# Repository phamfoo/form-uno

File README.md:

# Form Uno
> Gasket mounted 5x12 column staggered keyboard

## Introduction
I designed this board with a few goals in mind:

### Ergonomic
The layout is based on the corne/cornelius by [foostan](https://github.com/foostan), with some adjustments:
- Unsplit.
- Number row.
- Options for dedicated arrow keys.

### Fully featured
It also comes with the neat features that you'd find in custom mechanical keyboards:

- Gasket-mounted.
- Hotswap PCB + daughterboard.
- Clean and minimal design.

### Easy to build
- Powered by an [RP2040 Tiny](https://www.waveshare.com/rp2040-tiny.htm) and [all the other parts](build) can be easily sourced.
- No tiny SMD components required!

## Build guide
See [build](/build)

## Thanks
- [JLCPCB](https://jlcpcb.com/?from=see) for providing the keyboard plate, 3D printed case, and PCB for this project. If you're looking to build your own board, I highly recommend their services.
- [foostan](https://github.com/foostan) for creating the corne/cornelius, which inspired this project in the first place.

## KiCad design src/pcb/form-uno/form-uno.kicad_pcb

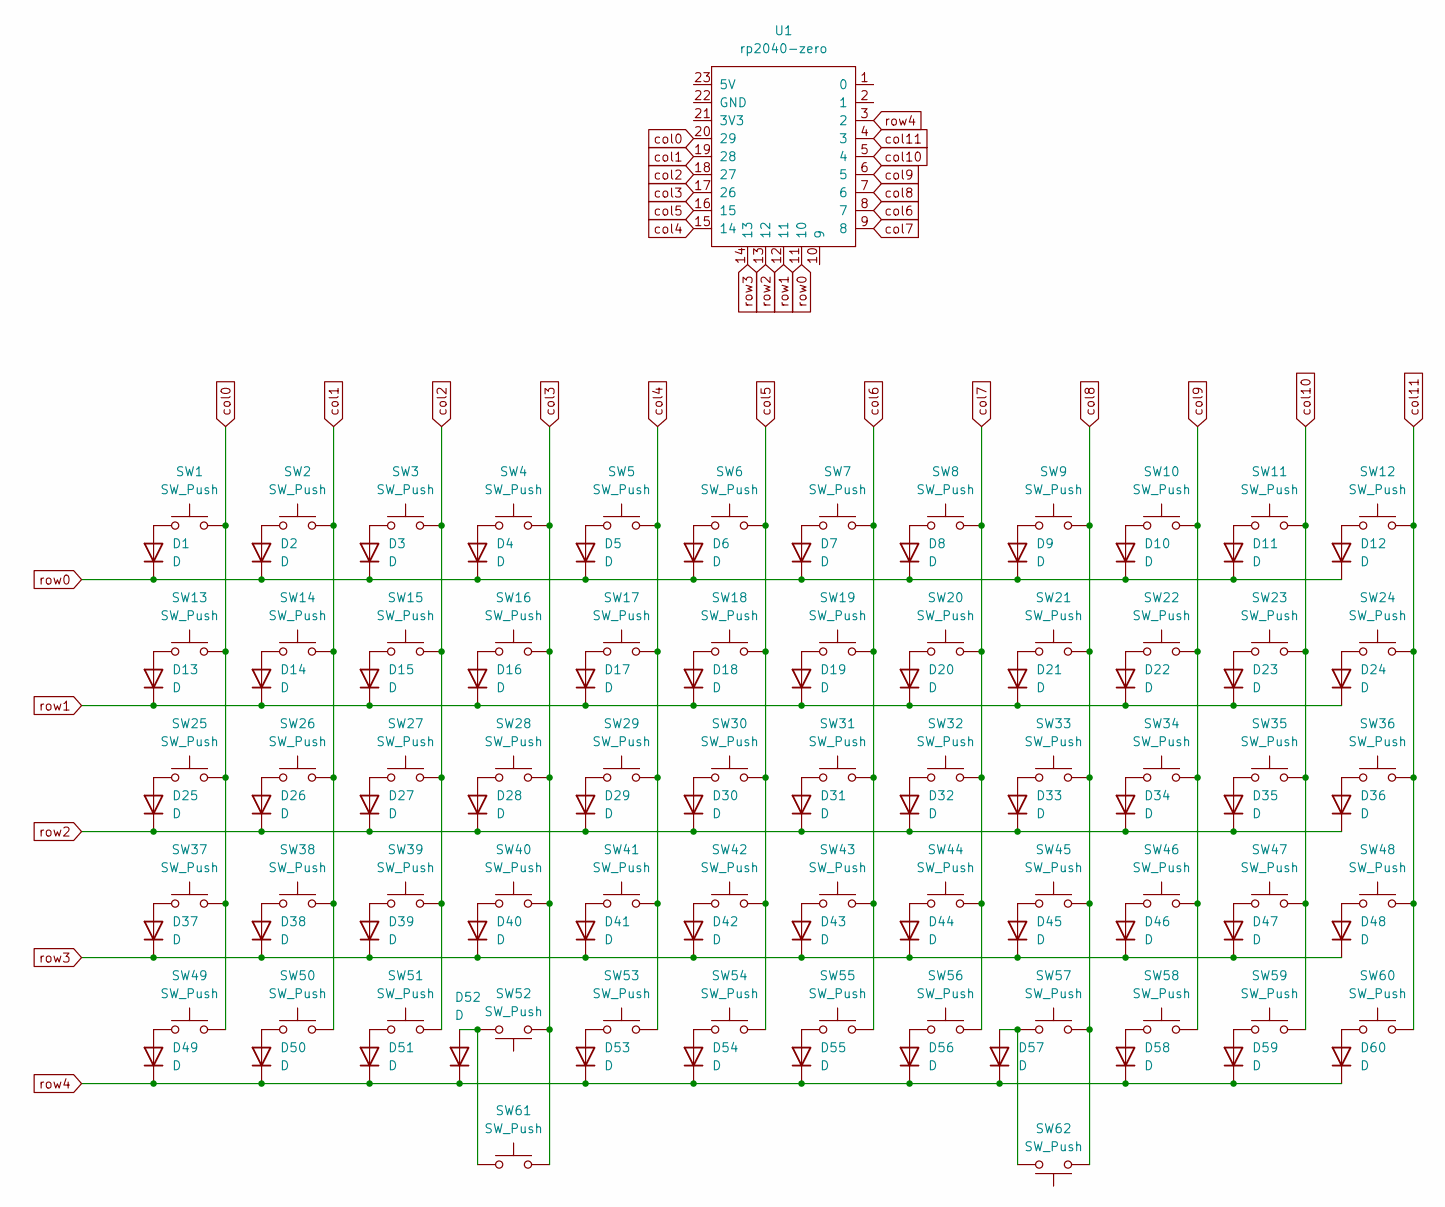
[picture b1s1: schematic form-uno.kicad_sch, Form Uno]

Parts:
D1, D2, D3, D4, D5, D6, D7, D8, D9, D10, D11, D12, D13, D14, D15, D16, D17, D18, D19, D20, D21, D22, D23, D24, D25, D26, D27, D28, D29, D30, D31, D32, D33, D34, D35, D36, D37, D38, D39, D40, D41, D42, D43, D44, D45, D46, D47, D48, D49, D50, D51, D52, D53, D54, D55, D56, D57, D58, D59, D60: D; D3_TH_SMD_v2
SW1, SW2, SW3, SW4, SW5, SW6, SW7, SW8, SW9, SW10, SW11, SW12, SW13, SW14, SW15, SW16, SW17, SW18, SW19, SW20, SW21, SW22, SW23, SW24, SW25, SW26, SW27, SW28, SW29, SW30, SW31, SW32, SW33, SW34, SW35, SW36, SW37, SW38, SW39, SW40, SW41, SW42, SW43, SW44, SW45, SW46, SW47, SW48, SW49, SW50, SW51, SW52, SW53, SW54, SW55, SW56, SW57, SW58, SW59, SW60, SW61, SW62: SW_Push; SW_MX_HS_CPG151101S11_1u
U1: rp2040-zero; rp2040-tiny

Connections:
unnamed: D1.2 (A), SW1.1
unnamed: D2.2 (A), SW2.1
unnamed: D3.2 (A), SW3.1
unnamed: D4.2 (A), SW4.1
unnamed: D5.2 (A), SW5.1
unnamed: D6.2 (A), SW6.1
unnamed: D7.2 (A), SW7.1
unnamed: D8.2 (A), SW8.1
unnamed: D9.2 (A), SW9.1
unnamed: D10.2 (A), SW10.1
unnamed: D11.2 (A), SW11.1
unnamed: D12.2 (A), SW12.1
unnamed: D13.2 (A), SW13.1
unnamed: D14.2 (A), SW14.1
unnamed: D15.2 (A), SW15.1
unnamed: D16.2 (A), SW16.1
unnamed: D17.2 (A), SW17.1
unnamed: D18.2 (A), SW18.1
unnamed: D19.2 (A), SW19.1
unnamed: D20.2 (A), SW20.1
unnamed: D21.2 (A), SW21.1
unnamed: D22.2 (A), SW22.1
unnamed: D23.2 (A), SW23.1
unnamed: D24.2 (A), SW24.1
unnamed: D25.2 (A), SW25.1
unnamed: D26.2 (A), SW26.1
unnamed: D27.2 (A), SW27.1
unnamed: D28.2 (A), SW28.1
unnamed: D29.2 (A), SW29.1
unnamed: D30.2 (A), SW30.1
unnamed: D31.2 (A), SW31.1
unnamed: D32.2 (A), SW32.1
unnamed: D33.2 (A), SW33.1
unnamed: D34.2 (A), SW34.1
unnamed: D35.2 (A), SW35.1
unnamed: D36.2 (A), SW36.1
unnamed: D37.2 (A), SW37.1
unnamed: D38.2 (A), SW38.1
unnamed: D39.2 (A), SW39.1
unnamed: D40.2 (A), SW40.1
unnamed: D41.2 (A), SW41.1
unnamed: D42.2 (A), SW42.1
unnamed: D43.2 (A), SW43.1
unnamed: D44.2 (A), SW44.1
unnamed: D45.2 (A), SW45.1
unnamed: D46.2 (A), SW46.1
unnamed: D47.2 (A), SW47.1
unnamed: D48.2 (A), SW48.1
unnamed: D49.2 (A), SW49.1
unnamed: D50.2 (A), SW50.1
unnamed: D51.2 (A), SW51.1
unnamed: D52.2 (A), SW52.2, SW61.1
unnamed: D53.2 (A), SW53.1
unnamed: D54.2 (A), SW54.1
unnamed: D55.2 (A), SW55.1
unnamed: D56.2 (A), SW56.1
unnamed: D57.2 (A), SW57.1, SW62.2
unnamed: D58.2 (A), SW58.1
unnamed: D59.2 (A), SW59.1
unnamed: D60.2 (A), SW60.1
col0: SW1.2, SW13.2, SW25.2, SW37.2, SW49.2, U1.20 (29)
col1: SW2.2, SW14.2, SW26.2, SW38.2, SW50.2, U1.19 (28)
col2: SW3.2, SW15.2, SW27.2, SW39.2, SW51.2, U1.18 (27)
col3: SW4.2, SW16.2, SW28.2, SW40.2, SW52.1, SW61.2, U1.17 (26)
col4: SW5.2, SW17.2, SW29.2, SW41.2, SW53.2, U1.15 (14)
col5: SW6.2, SW18.2, SW30.2, SW42.2, SW54.2, U1.16 (15)
col6: SW7.2, SW19.2, SW31.2, SW43.2, SW55.2, U1.8 (7)
col7: SW8.2, SW20.2, SW32.2, SW44.2, SW56.2, U1.9 (8)
col8: SW9.2, SW21.2, SW33.2, SW45.2, SW57.2, SW62.1, U1.7 (6)
col9: SW10.2, SW22.2, SW34.2, SW46.2, SW58.2, U1.6 (5)
col10: SW11.2, SW23.2, SW35.2, SW47.2, SW59.2, U1.5 (4)
col11: SW12.2, SW24.2, SW36.2, SW48.2, SW60.2, U1.4 (3)
row0: D1.1 (K), D2.1 (K), D3.1 (K), D4.1 (K), D5.1 (K), D6.1 (K), D7.1 (K), D8.1 (K), D9.1 (K), D10.1 (K), D11.1 (K), D12.1 (K), U1.11 (10)
row1: D13.1 (K), D14.1 (K), D15.1 (K), D16.1 (K), D17.1 (K), D18.1 (K), D19.1 (K), D20.1 (K), D21.1 (K), D22.1 (K), D23.1 (K), D24.1 (K), U1.12 (11)
row2: D25.1 (K), D26.1 (K), D27.1 (K), D28.1 (K), D29.1 (K), D30.1 (K), D31.1 (K), D32.1 (K), D33.1 (K), D34.1 (K), D35.1 (K), D36.1 (K), U1.13 (12)
row3: D37.1 (K), D38.1 (K), D39.1 (K), D40.1 (K), D41.1 (K), D42.1 (K), D43.1 (K), D44.1 (K), D45.1 (K), D46.1 (K), D47.1 (K), D48.1 (K), U1.14 (13)
row4: D49.1 (K), D50.1 (K), D51.1 (K), D52.1 (K), D53.1 (K), D54.1 (K), D55.1 (K), D56.1 (K), D57.1 (K), D58.1 (K), D59.1 (K), D60.1 (K), U1.3 (2)

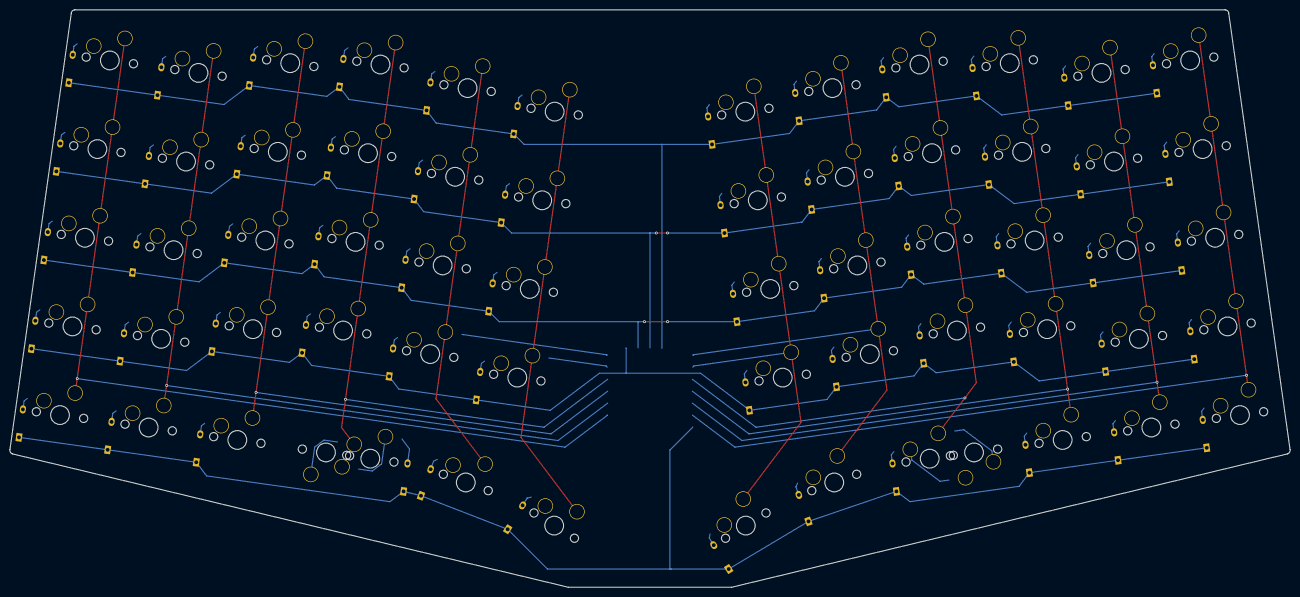
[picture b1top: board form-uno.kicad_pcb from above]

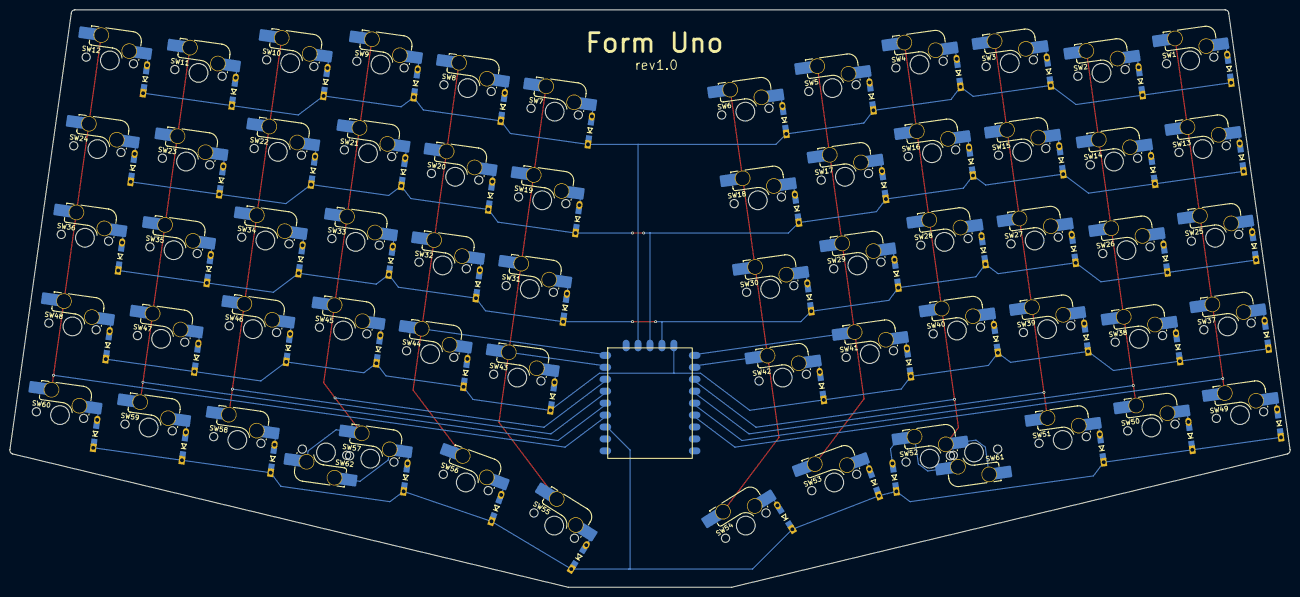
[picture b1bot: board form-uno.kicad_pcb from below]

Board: 2 copper layers, 272.4 x 122.9 mm, 123 parts (123 on the bottom side), 77 nets.

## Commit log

2024-06-29 Add schematic and position the keys
2024-06-29 Route the board matrix
2024-07-04 Route the rows and cols to microcontroller
2024-07-04 Add rounded corners
2024-07-27 Update rp2040 tiny footprint
2024-08-02 Set pcb revision
2024-08-02 Add build files
2024-08-10 Add build guide and README
2024-08-10 Add LICENSE
2024-09-02 Add matrix pins
2024-09-08 keymaps
2024-09-09 init keympa
